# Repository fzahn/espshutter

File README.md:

#ESP Shutter Control

This project was created to adapt a ESP8266 SoC with an existing Remote Control for controlling Schellenberg smart roller shutter drives (Prem 10/20/40)
The remote is a 5-channel remote with 4 buttons: UP/STOP/DOWN/change channel

The ESP has been connected to the remote control with a CD4066 chip, that is used as bipoloar switch to replace the existing four buttons.
The ESP uses GPIO 0-4 to switch the CD4066 chip.

The ESP can be configured using webinterface with MDNS-URL http://rolladen.local after it has gone through AUTO-Setup routine

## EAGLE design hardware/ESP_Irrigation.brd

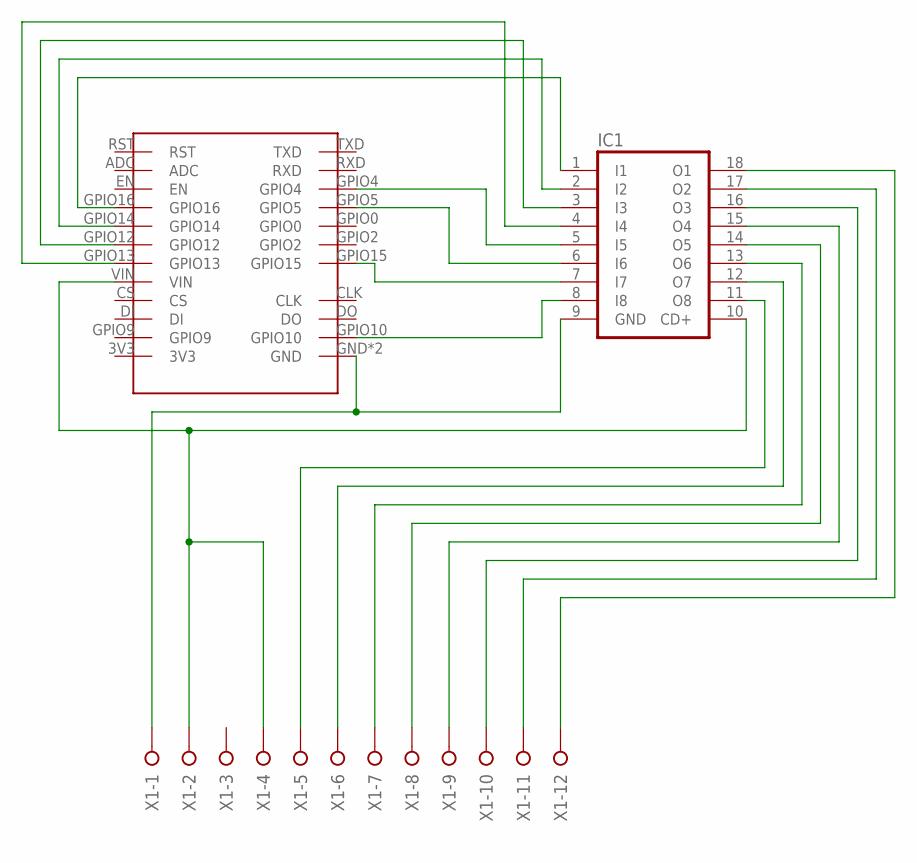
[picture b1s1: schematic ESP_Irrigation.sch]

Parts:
IC1: ULN2803A; DIL18
U$1: ESP12ADAPTERBOARD
X1: W237-12P

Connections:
unnamed: IC1.17 (O2), X1.11
unnamed: IC1.9 (GND), U$1.GND, U$1.GND1 (GND), X1.1
unnamed: IC1.11 (O8), X1.5
unnamed: IC1.8 (I8), U$1.GPIO10
unnamed: IC1.7 (I7), U$1.GPIO15
unnamed: IC1.5 (I5), U$1.GPIO4
unnamed: IC1.6 (I6), U$1.GPIO5
unnamed: IC1.4 (I4), U$1.GPIO13
unnamed: IC1.3 (I3), U$1.GPIO12
unnamed: IC1.12 (O7), X1.6
unnamed: IC1.13 (O6), X1.7
unnamed: IC1.14 (O5), X1.8
unnamed: IC1.15 (O4), X1.9
unnamed: IC1.16 (O3), X1.10
unnamed: IC1.10 (CD+), U$1.VIN, X1.2, X1.4
unnamed: IC1.18 (O1), X1.12
unnamed: IC1.1 (I1), U$1.GPIO16
unnamed: IC1.2 (I2), U$1.GPIO14

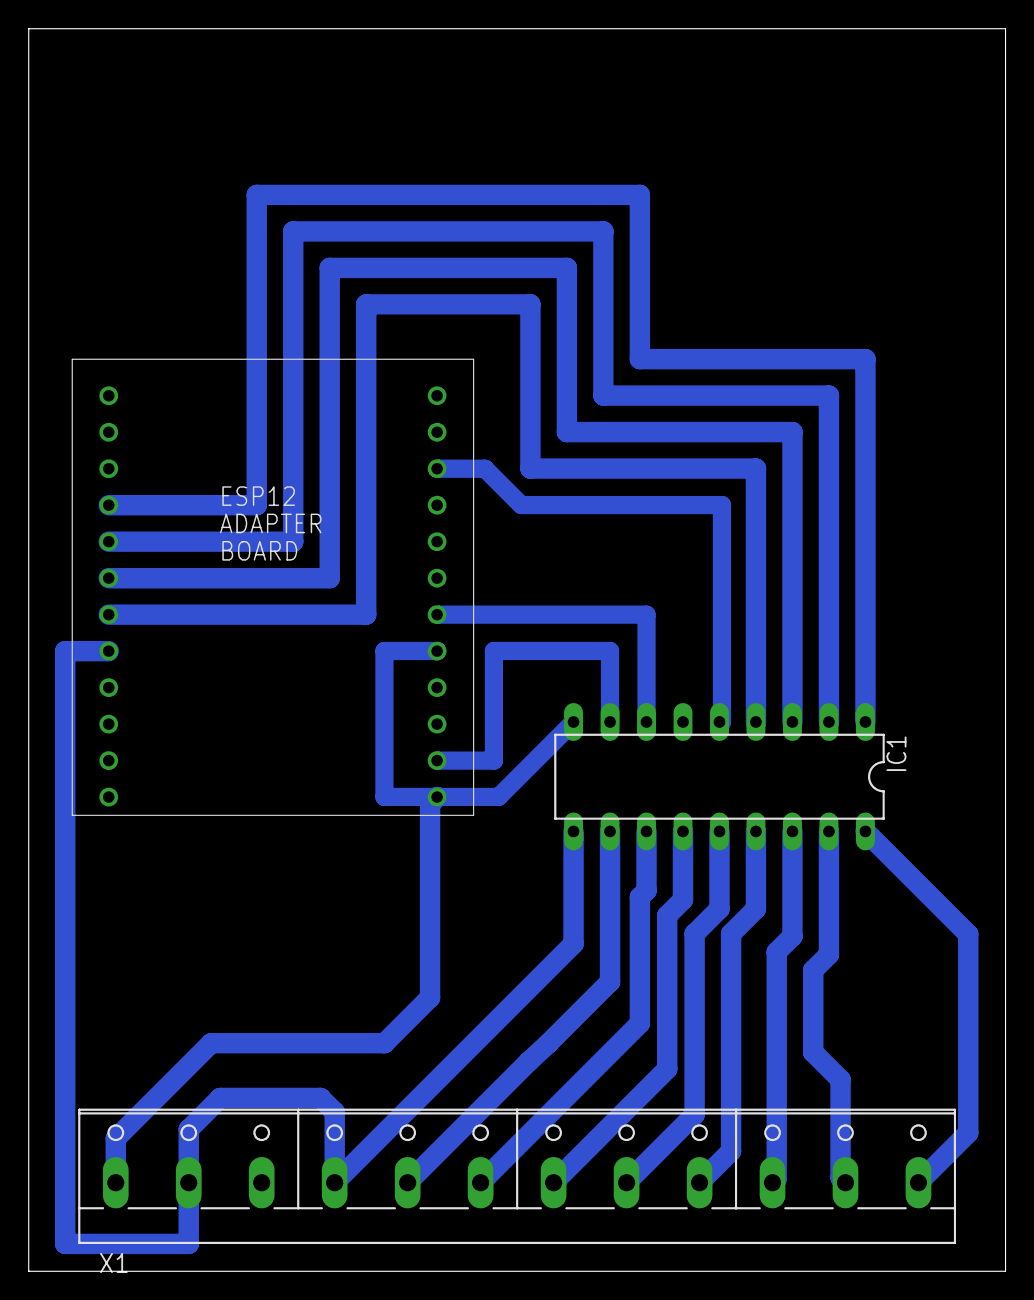
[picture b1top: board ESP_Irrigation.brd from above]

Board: 2 copper layers, 68.0 x 86.5 mm, 3 parts (0 on the bottom side), 18 nets.

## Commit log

2017-03-31 First working release
2017-04-03 Function movemiddle to getthe shutter half down (double click on down-button)
2017-04-03 MQTT for Middle position
2017-04-03 corrected code error
2017-04-03 MQTT-function for stop
2017-04-21 Modified version to control garden irrigation valves
2017-04-21 Fixing errors
2017-04-21 Fixed small errors, new Valve->GPIO table, added hardware
2017-04-21 adapted to new hardware-layout (GPIO to Valve)
2017-05-05 changed logic to get feedback and to shutdown everything on startup
2017-05-06 Failsave mode added: Valve 1 will definitely shutdown after 60 minutes, because of reasons....
2018-07-08 Now able to drive rollershutters to percent positions.
